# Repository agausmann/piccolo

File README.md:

# piccolo

A Raspberry Pi Pico clone with a USB-C port.

It's _\[current year\]_. Micro-USB is old news. But board designers are, for
some reason, still using it. I dunno, it might be a little cheaper/simpler.
Maybe you don't _technically_ need USB-C anway if you're not using USB 3.0.
But, in my experience, USB-C is just so much better; there is hardly any
reason to not use it.

## License

In the spirit of the original Pico design:

These design files are made available openly, with no limitations.

Permission to use, copy, modify, and/or distribute this design for
any purpose with or without fee is hereby granted.

THE DESIGN IS PROVIDED "AS IS" AND THE AUTHOR DISCLAIMS ALL WARRANTIES
WITH REGARD TO THIS DESIGN INCLUDING ALL IMPLIED WARRANTIES OF
MERCHANTABILITY AND FITNESS. IN NO EVENT SHALL THE AUTHOR BE LIABLE
FOR ANY SPECIAL, DIRECT, INDIRECT, OR CONSEQUENTIAL DAMAGES OR ANY
DAMAGES WHATSOEVER RESULTING FROM LOSS OF USE, DATA OR PROFITS, WHETHER
IN AN ACTION OF CONTRACT, NEGLIGENCE OR OTHER TORTIOUS ACTION, ARISING
OUT OF OR IN CONNECTION WITH THE USE OR PERFORMANCE OF THIS DESIGN.

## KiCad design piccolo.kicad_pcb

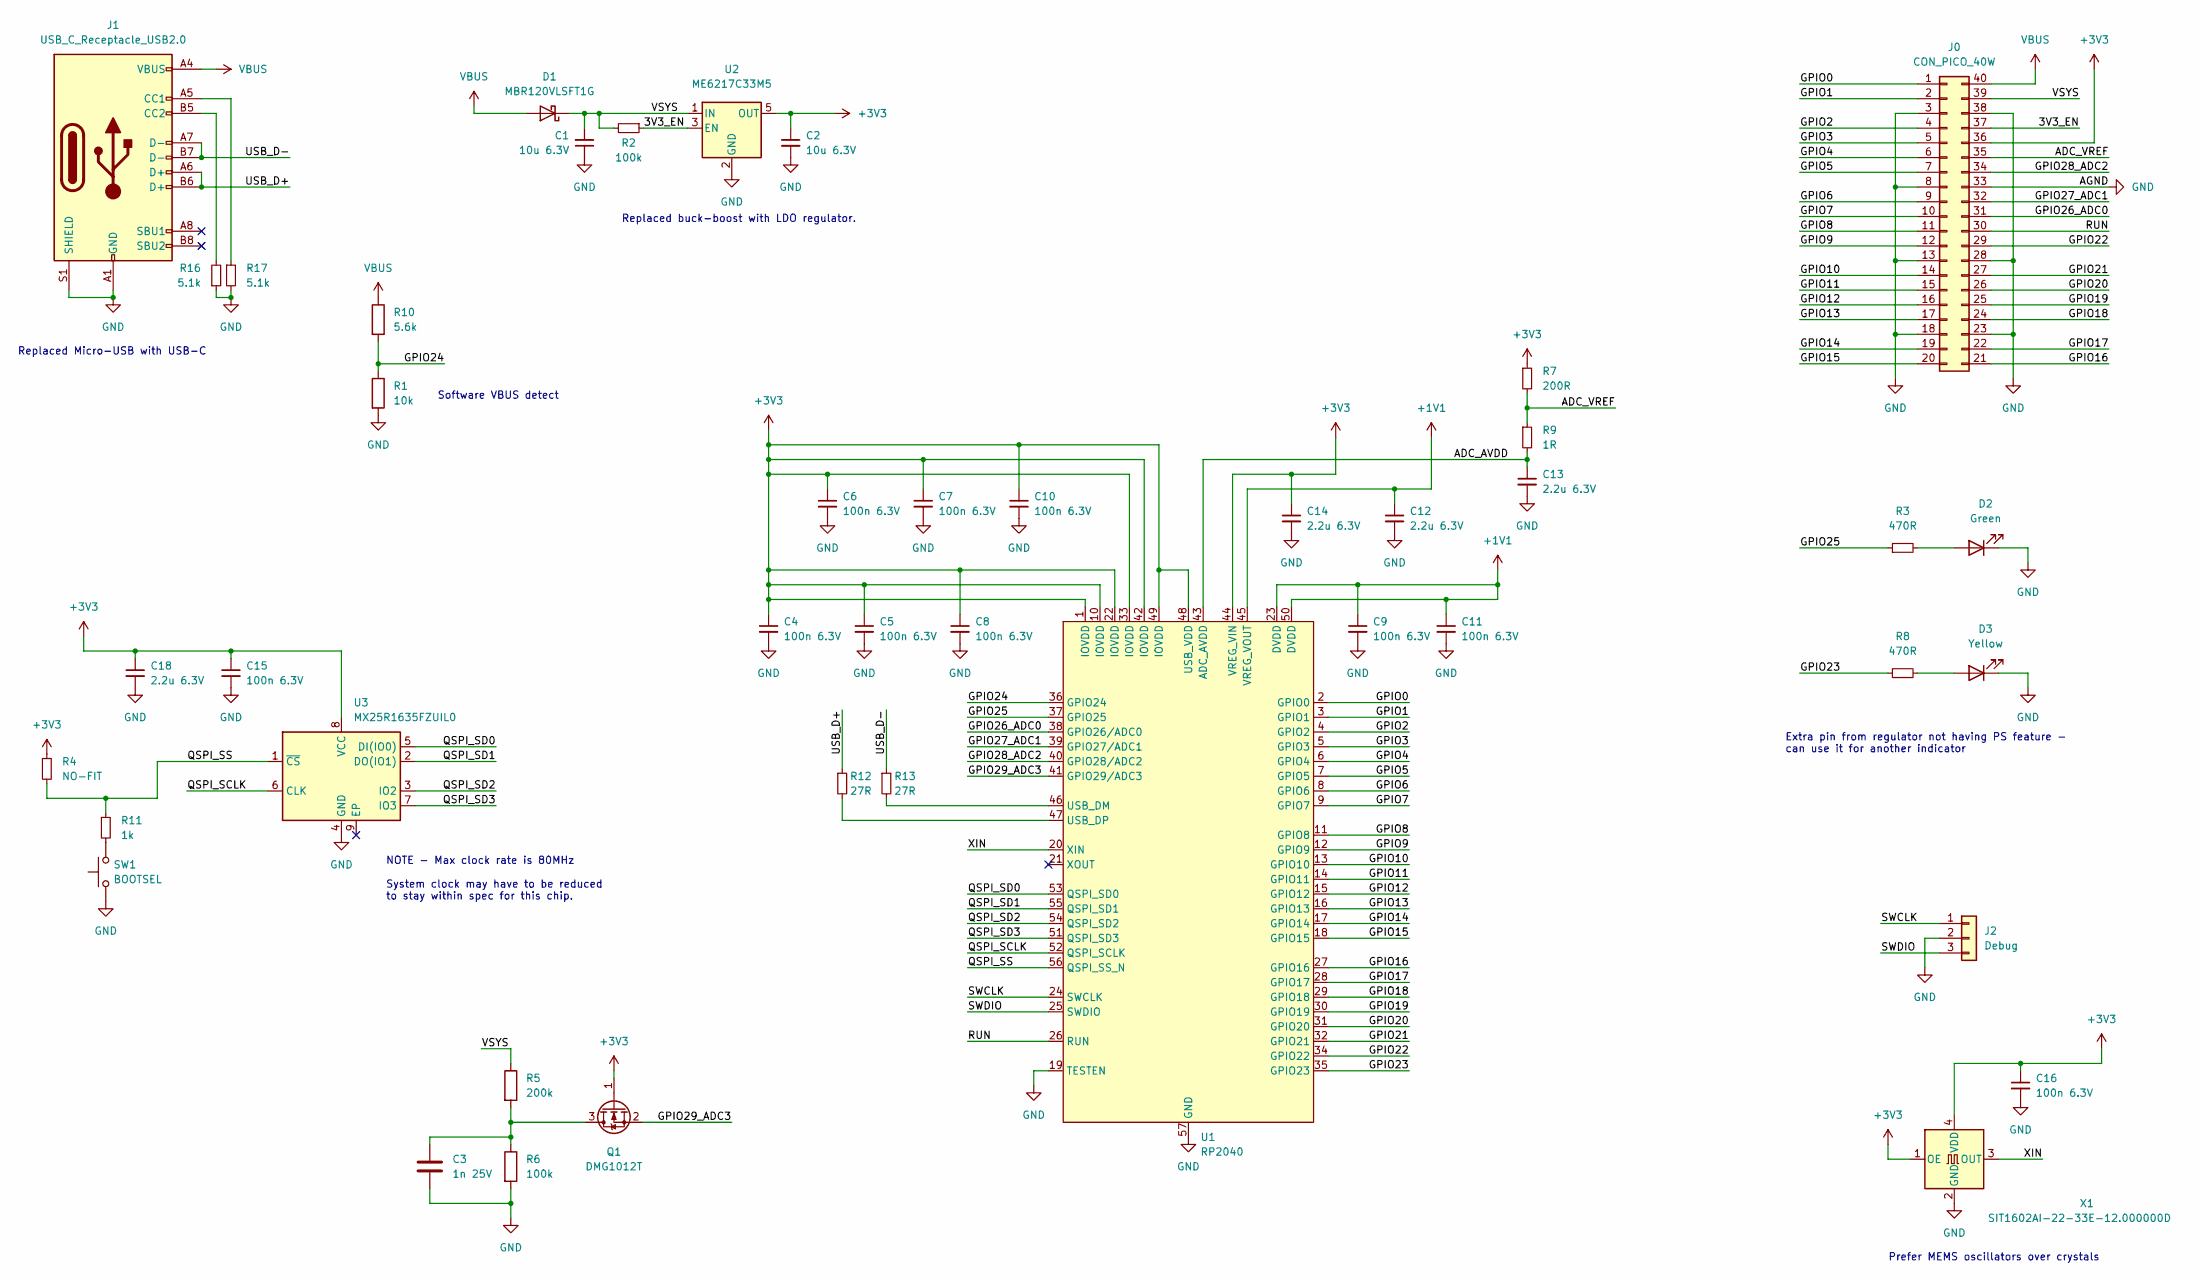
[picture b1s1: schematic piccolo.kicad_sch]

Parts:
C1, C2: 10u 6.3V; C_0805_2012Metric; LCSC C440198
C3: 1n 25V; C_0402_1005Metric; LCSC C66942
C4, C5, C6, C7, C8, C9, C10, C11, C15, C16: 100n 6.3V; C_0201_0603Metric; LCSC C160831
C12, C13, C14, C18: 2.2u 6.3V; C_0402_1005Metric; LCSC C12530
D1: MBR120VLSFT1G; D_SOD-123F; LCSC C123070
D2: Green; LED_0603_1608Metric; LCSC C72043
D3: Yellow; LED_0603_1608Metric; LCSC C72043
J0: CON_PICO_40W; RaspberryPi_Pico_OutlineAndPads
J1: USB_C_Receptacle_USB2.0; USB_C_Receptacle_HRO_TYPE-C-31-M-12; LCSC C165948
J2: Debug; PinHeader_1x03_P2.54mm_Vertical
Q1: DMG1012T; SOT-523; LCSC C2830301
R1: 10k; R_0402_1005Metric; LCSC C25744
R2, R6: 100k; R_0402_1005Metric; LCSC C25741
R3, R8: 470R; R_0402_1005Metric; LCSC C25117
R4: NO-FIT; R_0402_1005Metric
R5: 200k; R_0402_1005Metric; LCSC C25764
R7: 200R; R_0603_1608Metric; LCSC C25087
R9: 1R; R_0402_1005Metric; LCSC C25086
R10: 5.6k; R_0402_1005Metric; LCSC C25908
R11: 1k; R_0402_1005Metric; LCSC C11702
R12, R13: 27R; R_0201_0603Metric; LCSC C25100
R16, R17: 5.1k; R_0402_1005Metric; LCSC C25905
SW1: BOOTSEL; SW_Push_1P1T_NO_Vertical_Wuerth_434133025816
U1: RP2040; RP2040_QFN-56-1EP_7x7mm_P0.4mm_EP3.2x3.2mm_ThermalVias; LCSC C2040
U2: ME6217C33M5; SOT-23-5; LCSC C427602
U3: MX25R1635FZUIL0; USON-8-1EP_3x2mm_P0.5mm_EP0.2x1.6mm; LCSC C152595
X1: SIT1602AI-22-33E-12.000000D; SiT1602xx-2_3.2x2.5mm; LCSC C29752

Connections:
+1V1: C9.1, C11.1, C12.1, U1.23 (DVDD), U1.45 (VREG_VOUT), U1.50 (DVDD)
+3V3: C2.1, C4.1, C5.1, C6.1, C7.1, C8.1, C10.1, C14.1, C15.1, C16.1, C18.1, J0.36, Q1.1 (G), R4.1, R7.1, U1.1 (IOVDD), U1.10 (IOVDD), U1.22 (IOVDD), U1.33 (IOVDD), U1.42 (IOVDD), U1.44 (VREG_VIN), U1.48 (USB_VDD), U1.49 (IOVDD), U2.5 (OUT), U3.8 (VCC), X1.1 (OE), X1.4 (VDD)
/3V3_EN: J0.37, R2.1, U2.3 (EN)
/ADC_AVDD: C13.1, R9.2, U1.43 (ADC_AVDD)
/ADC_VREF: J0.35, R7.2, R9.1
/GPIO0: J0.1, U1.2 (GPIO0)
/GPIO1: J0.2, U1.3 (GPIO1)
/GPIO2: J0.4, U1.4 (GPIO2)
/GPIO3: J0.5, U1.5 (GPIO3)
/GPIO4: J0.6, U1.6 (GPIO4)
/GPIO5: J0.7, U1.7 (GPIO5)
/GPIO6: J0.9, U1.8 (GPIO6)
/GPIO7: J0.10, U1.9 (GPIO7)
/GPIO8: J0.11, U1.11 (GPIO8)
/GPIO9: J0.12, U1.12 (GPIO9)
/GPIO10: J0.14, U1.13 (GPIO10)
/GPIO11: J0.15, U1.14 (GPIO11)
/GPIO12: J0.16, U1.15 (GPIO12)
/GPIO13: J0.17, U1.16 (GPIO13)
/GPIO14: J0.19, U1.17 (GPIO14)
/GPIO15: J0.20, U1.18 (GPIO15)
/GPIO16: J0.21, U1.27 (GPIO16)
/GPIO17: J0.22, U1.28 (GPIO17)
/GPIO18: J0.24, U1.29 (GPIO18)
/GPIO19: J0.25, U1.30 (GPIO19)
/GPIO20: J0.26, U1.31 (GPIO20)
/GPIO21: J0.27, U1.32 (GPIO21)
/GPIO22: J0.29, U1.34 (GPIO22)
/GPIO23: R8.1, U1.35 (GPIO23)
/GPIO24: R1.1, R10.2, U1.36 (GPIO24)
/GPIO25: R3.1, U1.37 (GPIO25)
/GPIO26_ADC0: J0.31, U1.38 (GPIO26/ADC0)
/GPIO27_ADC1: J0.32, U1.39 (GPIO27/ADC1)
/GPIO28_ADC2: J0.34, U1.40 (GPIO28/ADC2)
/GPIO29_ADC3: Q1.2 (S), U1.41 (GPIO29/ADC3)
/QSPI_SCLK: U1.52 (QSPI_SCLK), U3.6 (CLK)
/QSPI_SD0: U1.53 (QSPI_SD0), U3.5 (DI(IO0))
/QSPI_SD1: U1.55 (QSPI_SD1), U3.2 (DO(IO1))
/QSPI_SD2: U1.54 (QSPI_SD2), U3.3 (IO2)
/QSPI_SD3: U1.51 (QSPI_SD3), U3.7 (IO3)
/QSPI_SS: R4.2, R11.1, U1.56 (QSPI_SS_N), U3.1 (~CS)
/RUN: J0.30, U1.26 (RUN)
/SWCLK: J2.1, U1.24 (SWCLK)
/SWDIO: J2.3, U1.25 (SWDIO)
/USB_D+: J1.A6 (D+), J1.B6 (D+), R12.1
/USB_D-: J1.A7 (D-), J1.B7 (D-), R13.1
/VSYS: C1.2, D1.1 (K), J0.39, R2.2, R5.1, U2.1 (IN)
/XIN: U1.20 (XIN), X1.3 (OUT)
GND: C1.1, C2.2, C3.2, C4.2, C5.2, C6.2, C7.2, C8.2, C9.2, C10.2, C11.2, C12.2, C13.2, C14.2, C15.2, C16.2, C18.2, D2.1 (K), D3.1 (K), J0.3, J0.8, J0.13, J0.18, J0.23, J0.28, J0.33, J0.38, J1.A1 (GND), J1.A12 (GND), J1.B1 (GND), J1.B12 (GND), J1.S1 (SHIELD), J2.2, R1.2, R6.2, R16.1, R17.2, SW1.1, U1.19 (TESTEN), U1.57 (GND), U2.2 (GND), U3.4 (GND), X1.2 (GND)
unnamed: C3.1, Q1.3 (D), R5.2, R6.1
unnamed: D2.2 (A), R3.2
unnamed: J1.A5 (CC1), R17.1
unnamed: J1.B5 (CC2), R16.2
unnamed: D3.2 (A), R8.2
unnamed: R11.2, SW1.2
unnamed: R12.2, U1.47 (USB_DP)
unnamed: R13.2, U1.46 (USB_DM)
VBUS: D1.2 (A), J0.40, J1.A4 (VBUS), J1.A9 (VBUS), J1.B4 (VBUS), J1.B9 (VBUS), R10.1

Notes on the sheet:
Replaced buck-boost with LDO regulator.
Prefer MEMS oscillators over crystals
Replaced Micro-USB with USB-C
Extra pin from regulator not having PS feature - can use it for another indicator
Software VBUS detect
NOTE - Max clock rate is 80MHz System clock may have to be reduced to stay within spec for this chip.

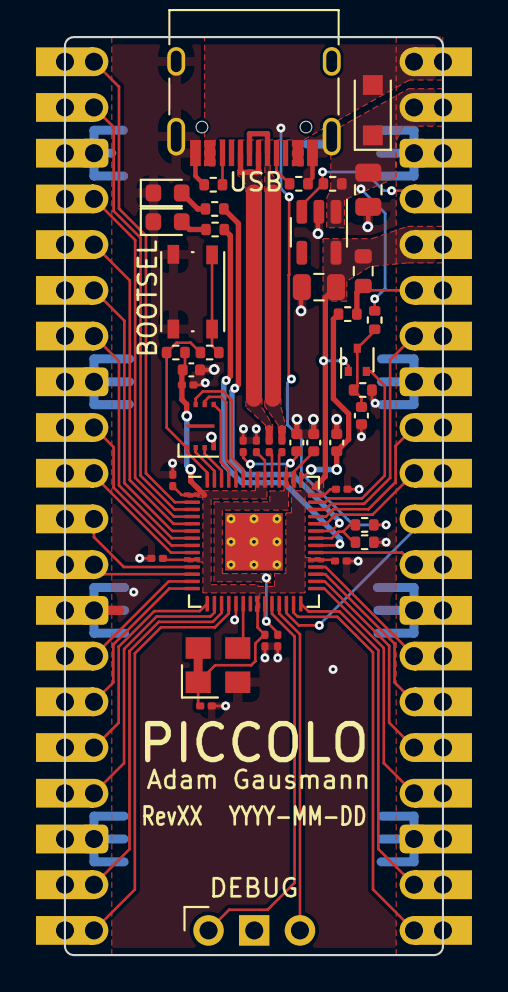
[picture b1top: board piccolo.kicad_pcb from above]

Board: 2 copper layers, 21.0 x 51.0 mm, 44 parts (0 on the bottom side), 58 nets.

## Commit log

2022-06-27 Port schematic and very roughly position components
2022-07-02 Initial PCB design
2022-07-02 Fill out BOM
